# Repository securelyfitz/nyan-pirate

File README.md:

nyan-pirate
===========

Bus Pirate + Nyan Cat

This has more extensive changes than the original nyan pirate

* the cat is on the 'bottom' of the pcb to have minimal change to the Bus Pirate design and have the rainbow cables come out from behind the cat.
* a different nyan cat bitmap was used to print a little better
* image and outline are changed in the dp_pcbs.lbr file
* in the process of adjusting everything to fit into the new board, a couple text labes are out of place (oops)
* i added two 1x1 .1" header points 20mm apart to hold a cr2032 battery holder. It's on a separate supply but shared ground
* i added 6 2x3 pin headers for LEDs:
  * pins 1 and 5 are ground
  * pin 3 connects to the battery
  * pins 2-4-6 are connected
  * In order to drive LEDs at full voltage, attach them from pin 3 to pin 1
  * in order to drive LEDs with a current limiting resistor, put the resistor from 3 to 4 and LEDs from 1-2 and 5-6
* i moved the USB connector to the edge of the board
* The Bsides Logo in silk/soldermask is in the nyan-pirate.lbr file. It's on layers 200 and 201
* the .cam file will put the 200 and 201 layers into the soldermask and silkscreen gerbers.

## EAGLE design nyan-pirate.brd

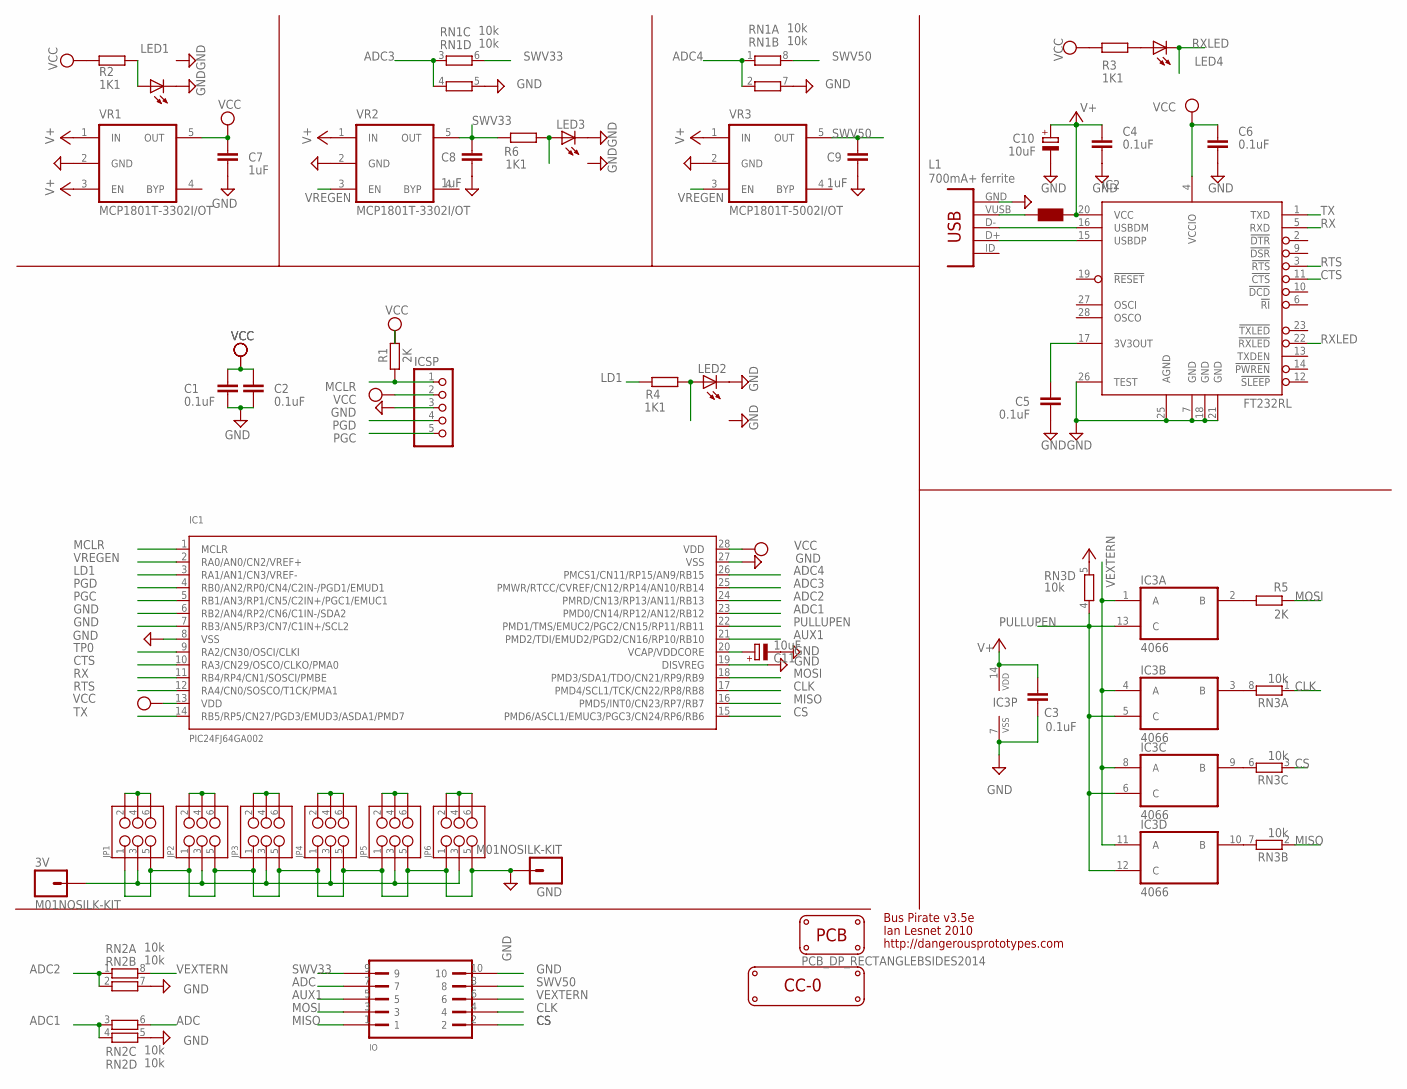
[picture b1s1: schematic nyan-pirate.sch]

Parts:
3V: M01NOSILK-KIT; 1X01NS-KIT
C1, C2, C3, C4, C5, C6: 0.1uF; C603
C7, C8, C9: 1uF; C603
C10, C11: 10uF; SMC_A
GND: M01NOSILK-KIT; 1X01NS-KIT
IC1: PIC24FJ64GA002; SSOP28
IC2: FT232RL; SSOP28
IC3: 4066; TSSOP14
ICSP: PINHD-1X5; 1X05
IO: HEADER2X5-SHRD-PTH-B; PINSHRD_PTH_2X05B
J1: CON-USB-MINI-BUSB1; CONN_USB_MINI-B
JP1, JP2, JP3, JP4, JP5, JP6: M03X2NO_SILK; 2X3-NS
L1: 700mA+ ferrite; WE-KI_0805_B
LED1, LED2, LED3, LED4: LEDCHIP-LED0805; CHIP-LED0805
LOGO1: LOGO_CC-0
PCB1: PCB_DP_RECTANGLEBSIDES2014; BIDESPDX2014
R1, R5: 2K; R603
R2, R3, R4, R6: 1K1; R603
RN1, RN2, RN3: 10k; RN8P-4R-CRA06S
VR1, VR2: MCP1801T-3302I/OT; SOT-23-5
VR3: MCP1801T-5002I/OT; SOT-23-5

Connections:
$N26: J1.VUSB, L1.2 (1)
ADC: IO.7, RN2.6 (2)
ADC1: IC1.23 (PMD0/CN14/RP12/AN12/RB12), RN2.3 (1), RN2.4 (1)
ADC2: IC1.24 (PMRD/CN13/RP13/AN11/RB13), RN2.1, RN2.2 (1)
ADC3: IC1.25 (PMWR/RTCC/CVREF/CN12/RP14/AN10/RB14), RN1.3 (1), RN1.4 (1)
ADC4: IC1.26 (PMCS1/CN11/RP15/AN9/RB15), RN1.1, RN1.2 (1)
AUX1: IC1.21 (PMD2/TDI/EMUD2/PGD2/CN16/RP10/RB10), IO.5
CLK: IC1.17 (PMD4/SCL1/TCK/CN22/RP8/RB8), IO.4, RN3.1
CS: IC1.15 (PMD6/ASCL1/EMUC3/PGC3/CN24/RP6/RB6), IO.2, RN3.3 (1)
CTS: IC1.10 (RA3/CN29/OSCO/CLKO/PMA0), IC2.11 (!CTS)
GND: C1.2, C2.2, C3.2, C4.2, C5.2, C6.2, C7.2, C8.2, C9.2, C10.-, C11.-, GND.1, IC1.6 (RB2/AN4/RP2/CN6/C1IN-/SDA2), IC1.7 (RB3/AN5/RP3/CN7/C1IN+/SCL2), IC1.8 (VSS), IC1.19 (DISVREG), IC1.27 (VSS), IC2.7 (GND), IC2.18 (GND), IC2.21 (GND), IC2.25 (AGND), IC2.26 (TEST), IC3.7 (VSS), ICSP.3, IO.10, J1.GND, JP1.1, JP1.5, JP2.1, JP2.5, JP3.1, JP3.5, JP4.1, JP4.5, JP5.1, JP5.5, JP6.1, JP6.5, LED1.C, LED2.C, LED3.C, RN1.5 (2), RN1.7 (2), RN2.5 (2), RN2.7 (2), VR1.2 (GND), VR2.2 (GND), VR3.2 (GND)
LD1: IC1.3 (RA1/AN1/CN3/VREF-), R4.2
MCLR: IC1.1 (MCLR), ICSP.1, R1.1
MISO: IC1.16 (PMD5/INT0/CN23/RP7/RB7), IO.1, RN3.2 (1)
MOSI: IC1.18 (PMD3/SDA1/TDO/CN21/RP9/RB9), IO.3, R5.1
unnamed: IC3.2 (B), R5.2
unnamed: IC3.9 (B), RN3.6 (2)
unnamed: C11.+, IC1.20 (VCAP/VDDCORE)
unnamed: IC3.10 (B), RN3.7 (2)
unnamed: IC3.3 (B), RN3.8 (2)
unnamed: LED2.A, R4.1
unnamed: LED1.A, R2.1
unnamed: JP1.2, JP1.4, JP1.6
unnamed: C5.1, IC2.17 (3V3OUT)
unnamed: JP2.2, JP2.4, JP2.6
unnamed: JP3.2, JP3.4, JP3.6
unnamed: JP4.2, JP4.4, JP4.6
unnamed: LED4.A, R3.1
unnamed: JP5.2, JP5.4, JP5.6
unnamed: IC2.15 (USBDP), J1.D+
unnamed: IC2.16 (USBDM), J1.D-
unnamed: JP6.2, JP6.4, JP6.6
unnamed: LED3.A, R6.1
unnamed: 3V.1, JP1.3, JP2.3, JP3.3, JP4.3, JP5.3, JP6.3
PGC: IC1.5 (RB1/AN3/RP1/CN5/C2IN+/PGC1/EMUC1), ICSP.5
PGD: IC1.4 (RB0/AN2/RP0/CN4/C2IN-/PGD1/EMUD1), ICSP.4
PULLUPEN: IC1.22 (PMD1/TMS/EMUC2/PGC2/CN15/RP11/RB11), IC3.5 (C), IC3.6 (C), IC3.12 (C), IC3.13 (C), RN3.4 (1)
RTS: IC1.12 (RA4/CN0/SOSCO/T1CK/PMA1), IC2.3 (!RTS)
RX: IC1.11 (RB4/RP4/CN1/SOSCI/PMBE), IC2.5 (RXD)
RXLED: IC2.22 (!RXLED), LED4.C
SWV33: C8.1, IO.9, R6.2, RN1.6 (2), VR2.5 (OUT)
SWV50: C9.1, IO.8, RN1.8 (2), VR3.5 (OUT)
TP0: IC1.9 (RA2/CN30/OSCI/CLKI)
TX: IC1.14 (RB5/RP5/CN27/PGD3/EMUD3/ASDA1/PMD7), IC2.1 (TXD)
V+: C3.1, C4.1, C10.+, IC2.20 (VCC), IC3.14 (VDD), L1.1 (2), RN3.5 (2), VR1.1 (IN), VR1.3 (EN), VR2.1 (IN), VR3.1 (IN)
VCC: C1.1, C2.1, C6.1, C7.1, IC1.13 (VDD), IC1.28 (VDD), IC2.4 (VCCIO), ICSP.2, R1.2, R2.2, R3.2, VR1.5 (OUT)
VEXTERN: IC3.1 (A), IC3.4 (A), IC3.8 (A), IC3.11 (A), IO.6, RN2.8 (2)
VREGEN: IC1.2 (RA0/AN0/CN2/VREF+), VR2.3 (EN), VR3.3 (EN)

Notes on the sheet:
Bus Pirate v3.5e
Ian Lesnet 2010
http://dangerousprototypes.com

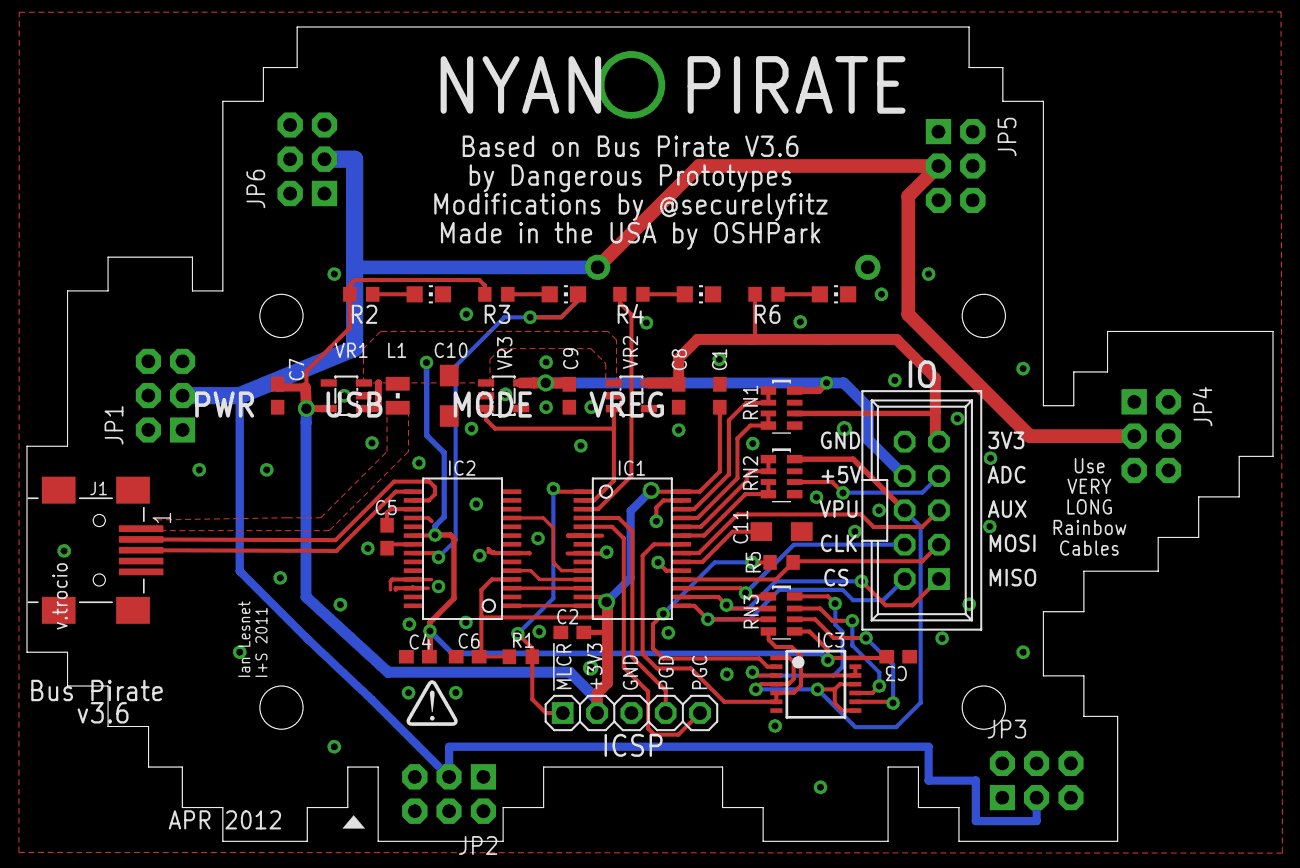
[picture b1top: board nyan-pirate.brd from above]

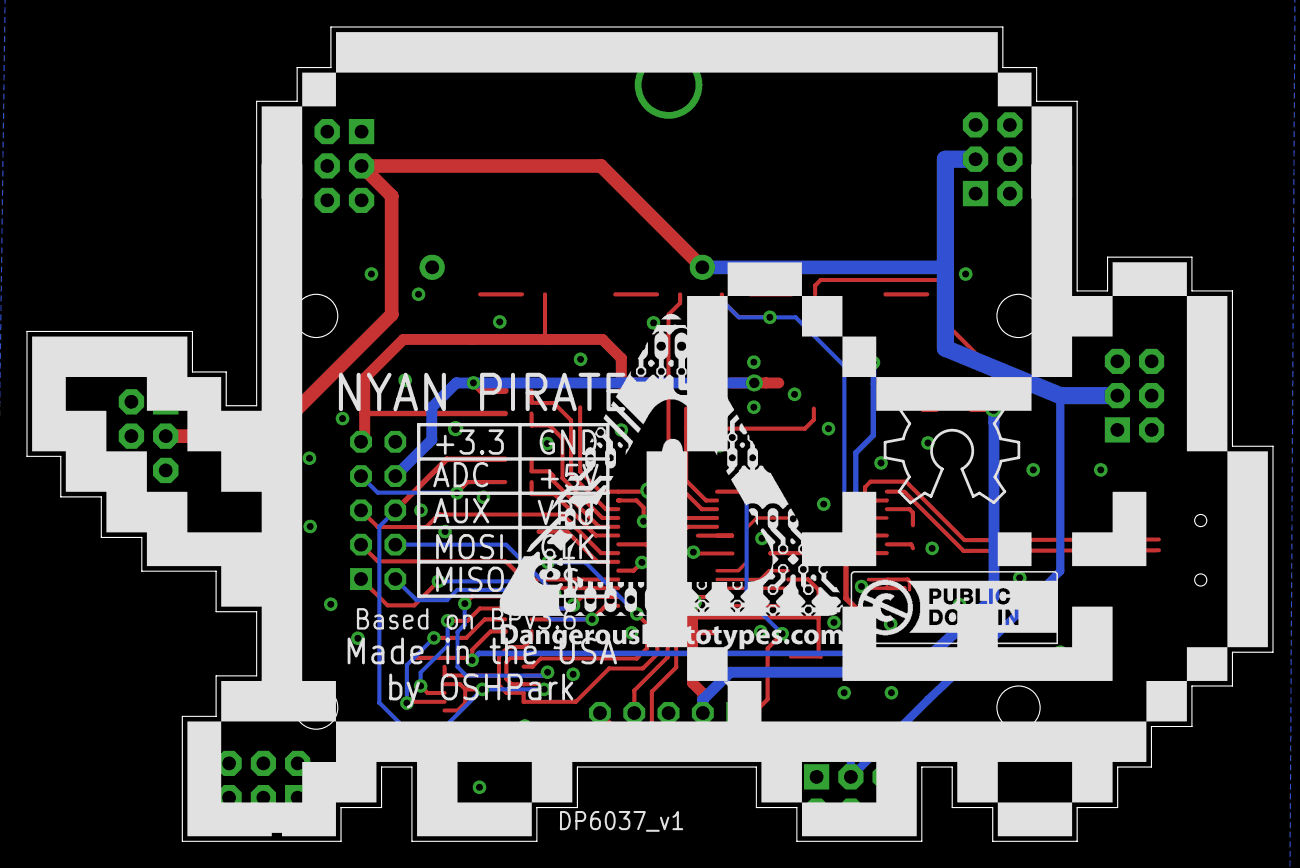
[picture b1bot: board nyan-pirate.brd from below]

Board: 2 copper layers, 92.2 x 60.3 mm, 48 parts (4 on the bottom side), 47 nets.

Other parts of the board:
U$1: DP-LOGO
U$2: OSHW_8X350_NOTEXT
U$3: DP_LOGO_ART_1X1
U$4: BSIDESPDXLOGO3

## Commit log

2014-09-30 initial commit of prototype nyan pirate based on BPv3.6
2014-09-30 changes to make special Bsides PDX 2014 version

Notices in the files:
parts and their libraries:
SparkFun-Connectors: Licensing: Creative Commons ShareAlike 4.0 International - https://creativecommons.org/licenses/by-sa/4.0
